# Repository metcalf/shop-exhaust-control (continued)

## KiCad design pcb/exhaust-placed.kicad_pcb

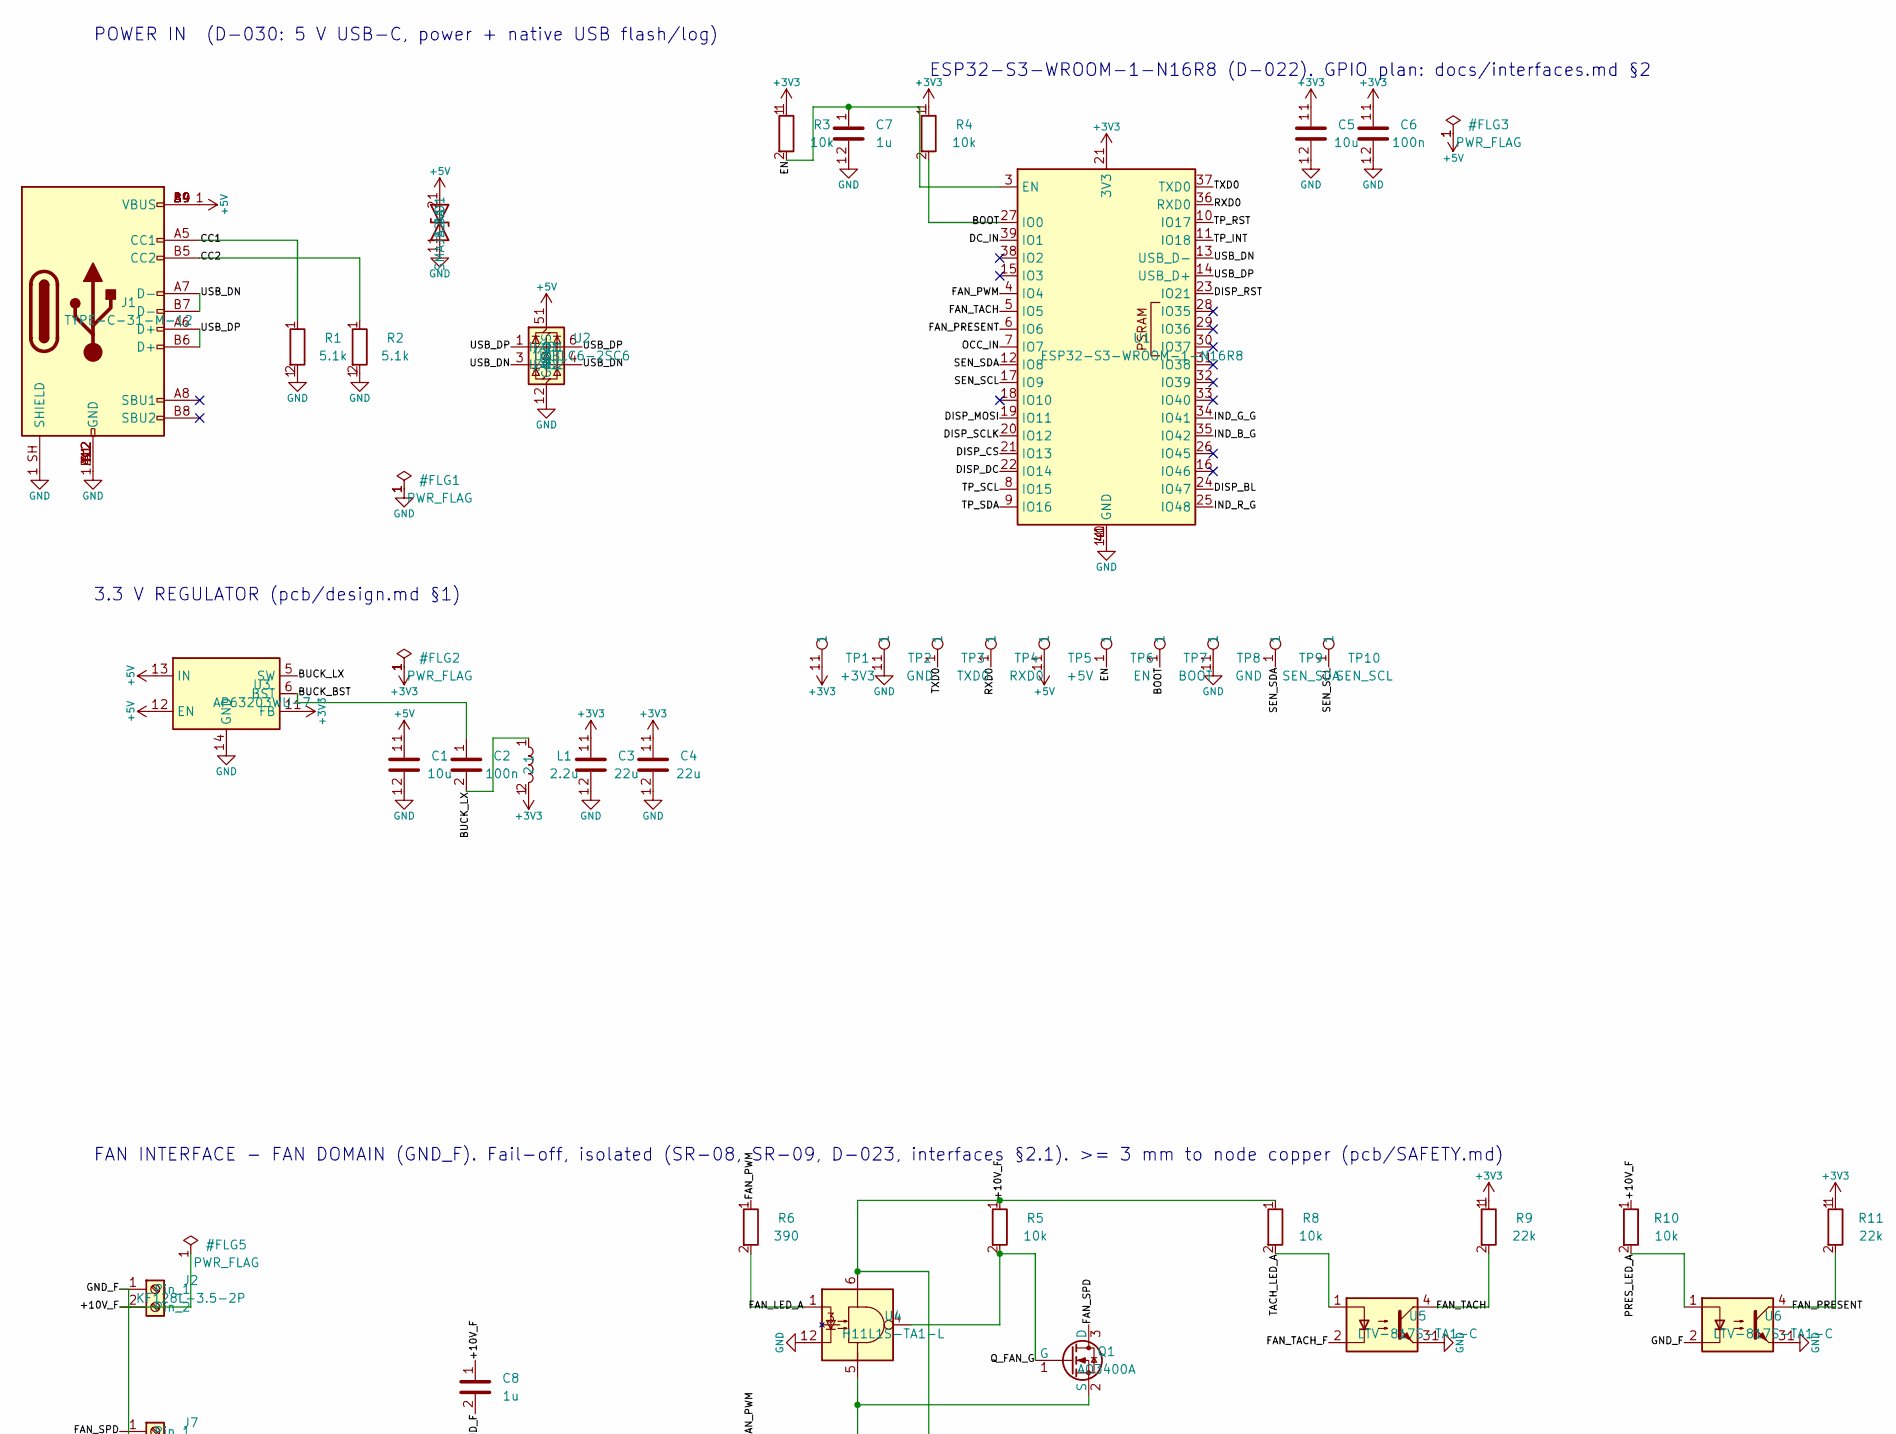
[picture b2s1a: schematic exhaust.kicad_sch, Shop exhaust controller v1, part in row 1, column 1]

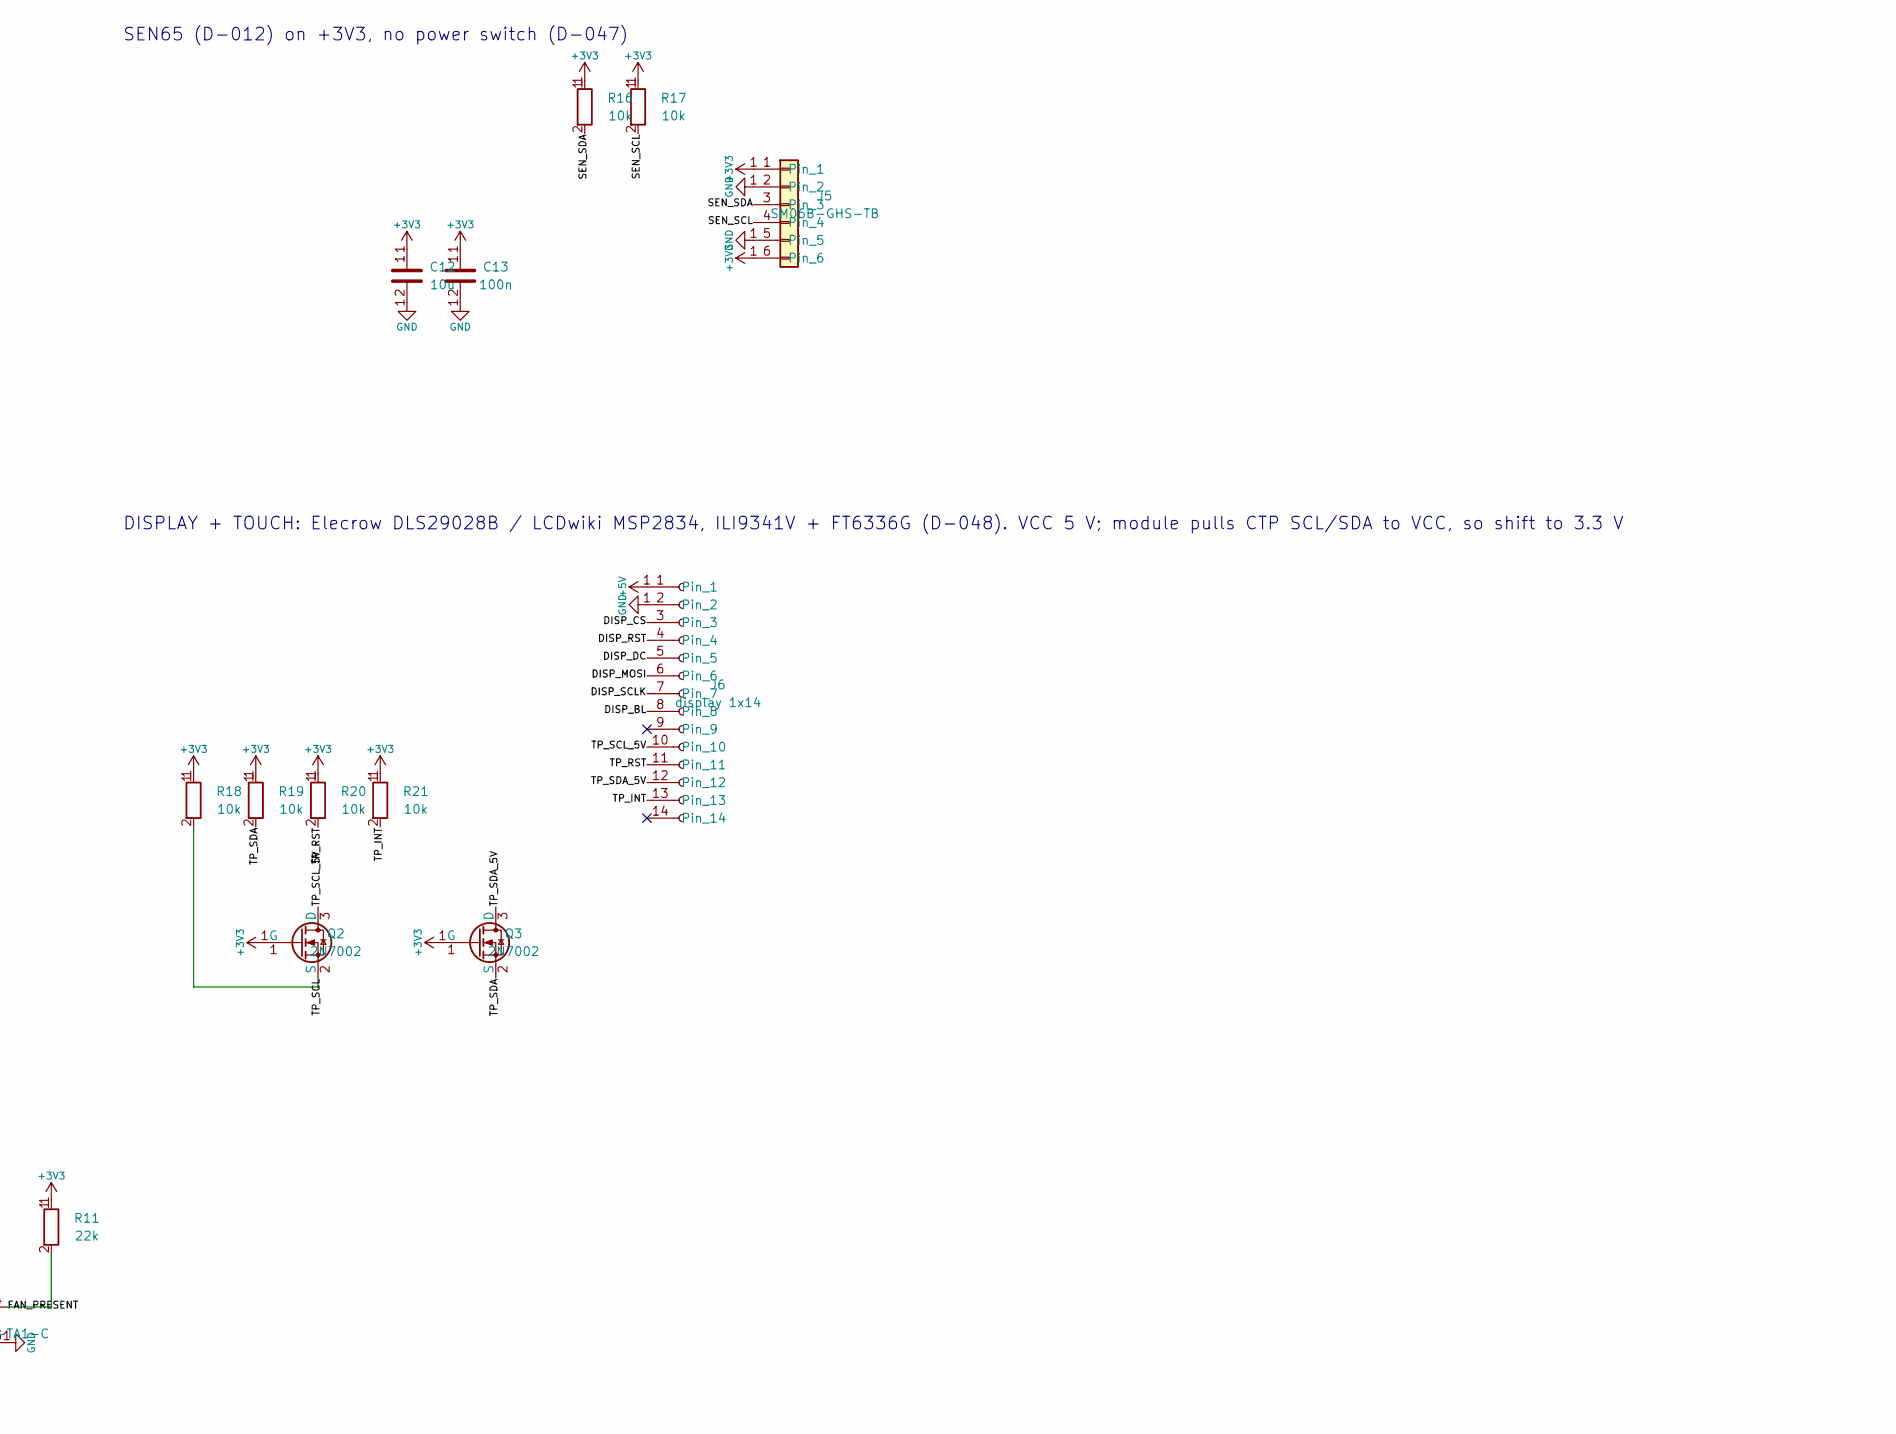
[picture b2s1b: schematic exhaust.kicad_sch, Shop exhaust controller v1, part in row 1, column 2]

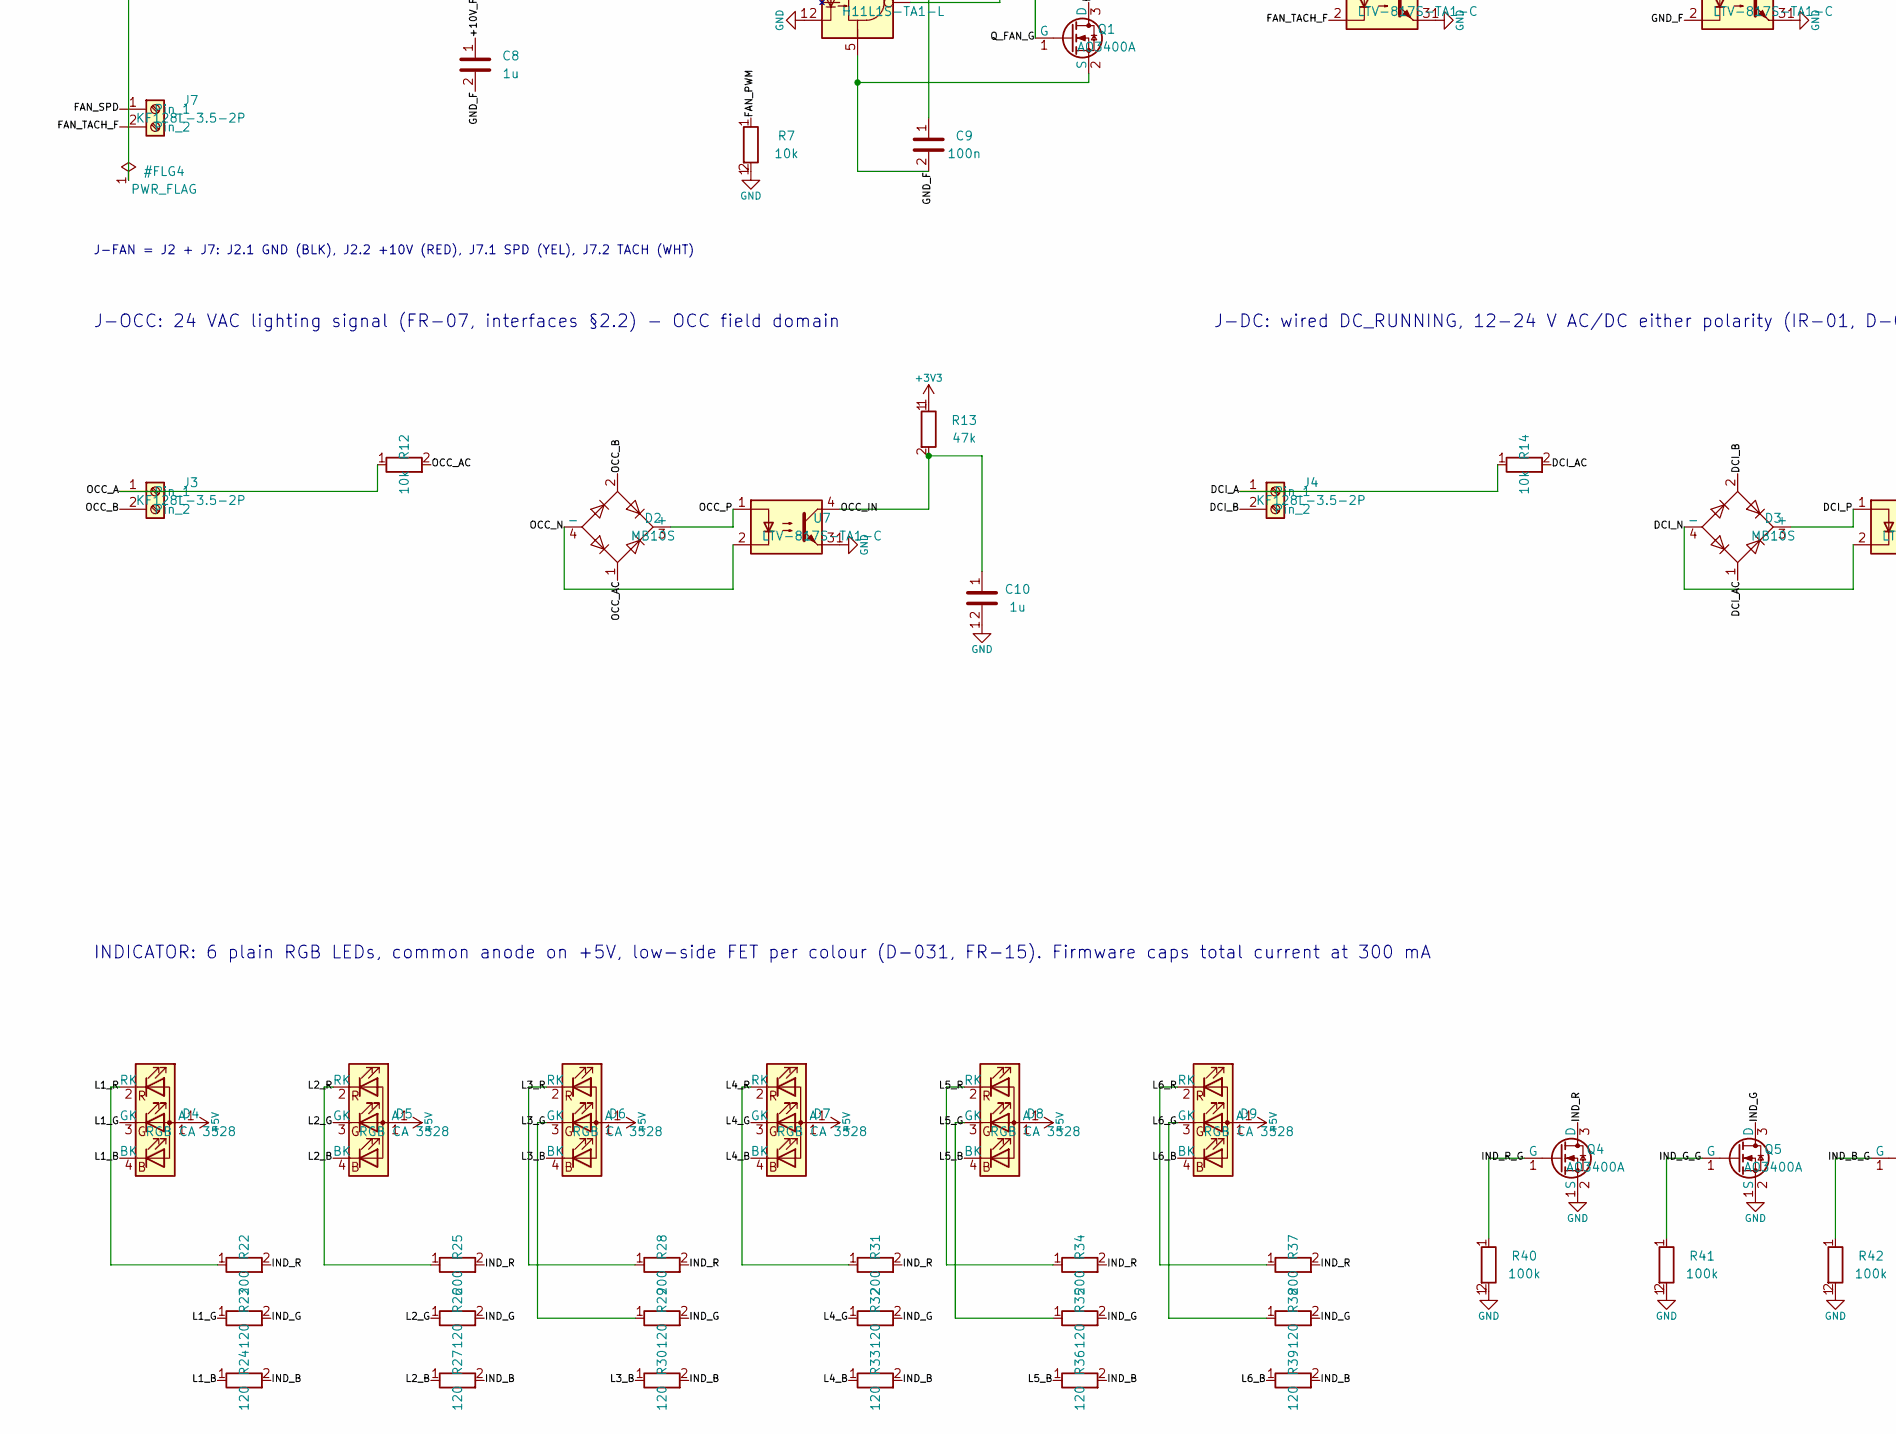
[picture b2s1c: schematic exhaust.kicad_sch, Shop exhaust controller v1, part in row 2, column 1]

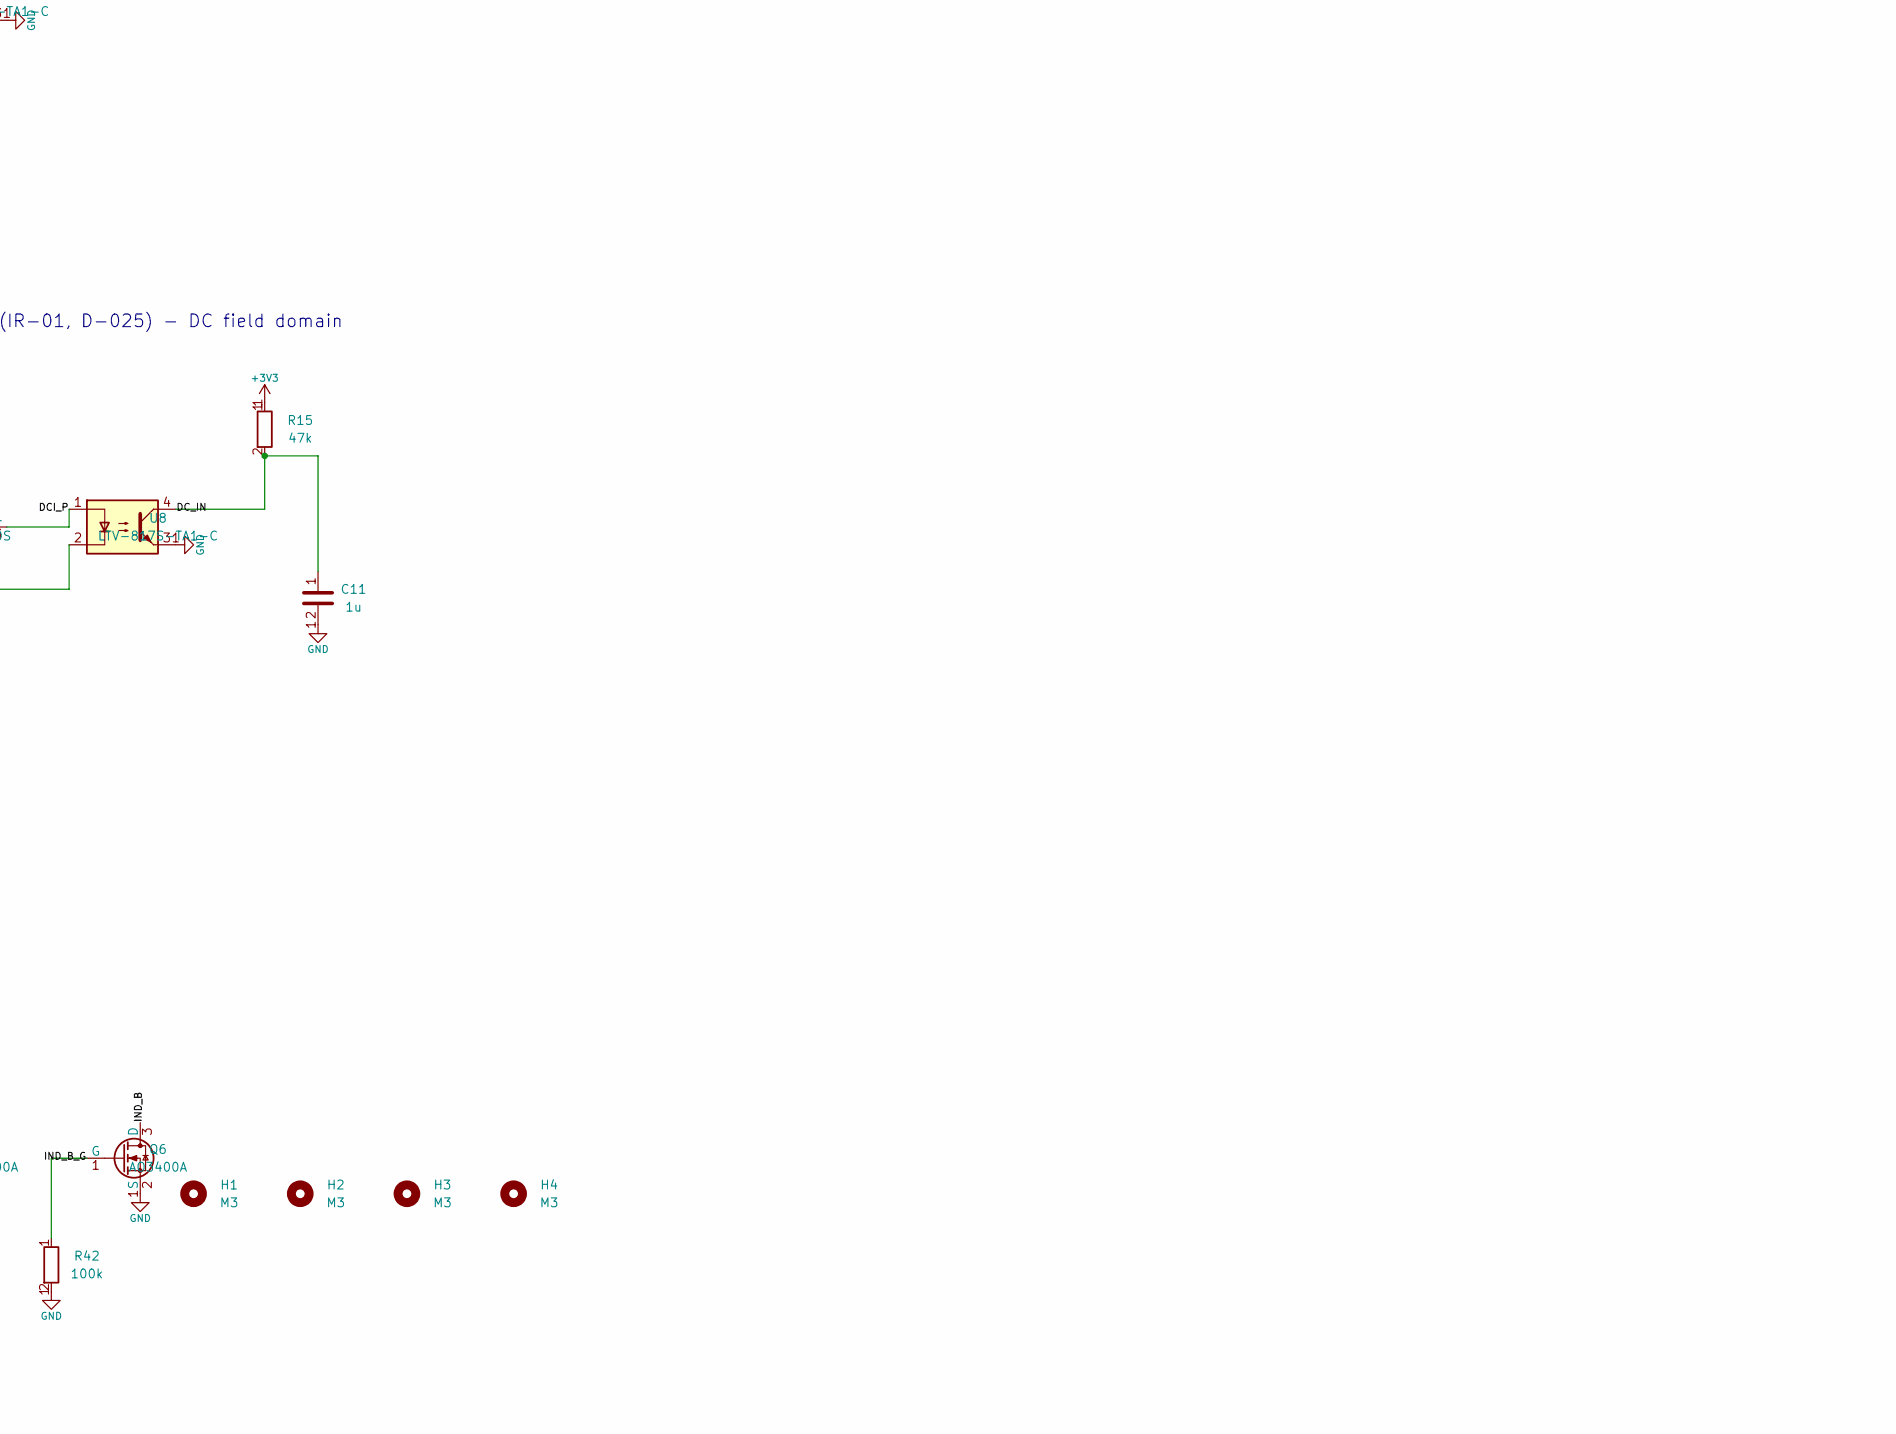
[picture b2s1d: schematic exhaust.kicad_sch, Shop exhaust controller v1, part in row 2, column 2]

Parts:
C1, C5, C12: 10u; C_0805_2012Metric
C2, C6, C9, C13: 100n; C_0603_1608Metric
C3, C4: 22u; C_1206_3216Metric
C7, C8, C10, C11: 1u; C_0603_1608Metric
D1: SMAJ5.0A; D_SMA; LCSC C113952
D2, D3: MB10S; Bridge_MBS_MB10S; LCSC C2488
D4, D5, D6, D7, D8, D9: RGB CA 3528; RGB_3528_TJ-S3528; LCSC C601699
H1, H2, H3, H4: M3; MountingHole_3.2mm_M3
J1: TYPE-C-31-M-12; USB_C_Receptacle_HRO_TYPE-C-31-M-12; LCSC C165948
J2, J3, J4, J7: KF128L-3.5-2P; TerminalBlock_KF128L-3.5-2P; LCSC C474930
J5: SM06B-GHS-TB; JST_GH_SM06B-GHS-TB_1x06-1MP_P1.25mm_Horizontal; LCSC C133065
J6: display 1x14; PinSocket_1x14_P2.54mm_Vertical; LCSC C2897377
L1: 2.2u; L_Murata_LQH44P; LCSC C135262
Q1, Q4, Q5, Q6: AO3400A; SOT-23; LCSC C20917
Q2, Q3: 2N7002; SOT-23; LCSC C8545
R1, R2: 5.1k; R_0603_1608Metric
R3, R4, R5, R7, R8, R10, R16, R17, R18, R19, R20, R21: 10k; R_0603_1608Metric
R6: 390; R_0603_1608Metric
R9, R11: 22k; R_0603_1608Metric
R12, R14: 10k; R_1206_3216Metric
R13, R15: 47k; R_0603_1608Metric
R22, R25, R28, R31, R34, R37: 200; R_0603_1608Metric
R23, R24, R26, R27, R29, R30, R32, R33, R35, R36, R38, R39: 120; R_0603_1608Metric
R40, R41, R42: 100k; R_0603_1608Metric
TP1: +3V3; TestPoint_Pad_D1.5mm
TP2, TP8: GND; TestPoint_Pad_D1.5mm
TP3: TXD0; TestPoint_Pad_D1.5mm
TP4: RXD0; TestPoint_Pad_D1.5mm
TP5: +5V; TestPoint_Pad_D1.5mm
TP6: EN; TestPoint_Pad_D1.5mm
TP7: BOOT; TestPoint_Pad_D1.5mm
TP9: SEN_SDA; TestPoint_Pad_D1.5mm
TP10: SEN_SCL; TestPoint_Pad_D1.5mm
U1: ESP32-S3-WROOM-1-N16R8; ESP32-S3-WROOM-1_NoEPADVias; LCSC C2913202
U2: USBLC6-2SC6; SOT-23-6; LCSC C2827654
U3: AP63203WU-7; TSOT-23-6; LCSC C780769
U4: H11L1S-TA1-L; SOP-6_H11L1S_LS10.2; LCSC C7435535
U5, U6, U7, U8: LTV-817S-TA1-C; SOP-4_LTV-817S_LS10.3; LCSC C109227

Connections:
+3V3: C3.1, C4.1, C5.1, C6.1, C12.1, C13.1, J5.1, J5.6, L1.2, Q2.1 (G), Q3.1 (G), R3.1, R4.1, R9.1, R11.1, R13.1, R15.1, R16.1, R17.1, R18.1, R19.1, R20.1, R21.1, TP1.1, U1.2 (3V3), U3.1 (FB)
+5V: C1.1, D1.2 (A2), D4.1 (A), D5.1 (A), D6.1 (A), D7.1 (A), D8.1 (A), D9.1 (A), J1.A4 (VBUS), J1.A9 (VBUS), J1.B4 (VBUS), J1.B9 (VBUS), J6.1, TP5.1, U2.5 (VBUS), U3.2 (EN), U3.3 (IN)
/+10V_F: C8.1, C9.1, J2.2, R5.1, R8.1, R10.1, U4.6
/BOOT: R4.2, TP7.1, U1.27 (IO0)
/BUCK_BST: C2.1, U3.6 (BST)
/BUCK_LX: C2.2, L1.1, U3.5 (SW)
/CC1: J1.A5 (CC1), R1.1
/CC2: J1.B5 (CC2), R2.1
/DCI_A: J4.1, R14.1
/DCI_AC: D3.1, R14.2
/DCI_B: D3.2, J4.2
/DCI_N: D3.4 (-), U8.2
/DCI_P: D3.3 (+), U8.1
/DC_IN: C11.1, R15.2, U1.39 (IO1), U8.4
/DISP_BL: J6.8, U1.24 (IO47)
/DISP_CS: J6.3, U1.21 (IO13)
/DISP_DC: J6.5, U1.22 (IO14)
/DISP_MOSI: J6.6, U1.19 (IO11)
/DISP_RST: J6.4, U1.23 (IO21)
/DISP_SCLK: J6.7, U1.20 (IO12)
/EN: C7.1, R3.2, TP6.1, U1.3 (EN)
/FAN_LED_A: R6.2, U4.1
/FAN_PRESENT: R11.2, U1.6 (IO6), U6.4
/FAN_PWM: R6.1, R7.1, U1.4 (IO4)
/FAN_SPD: J7.1, Q1.3 (D)
/FAN_TACH: R9.2, U1.5 (IO5), U5.4
/FAN_TACH_F: J7.2, U5.2
/GND_F: C8.2, C9.2, J2.1, Q1.2 (S), U4.5, U6.2
/IND_B: Q6.3 (D), R24.2, R27.2, R30.2, R33.2, R36.2, R39.2
/IND_B_G: Q6.1 (G), R42.1, U1.35 (IO42)
/IND_G: Q5.3 (D), R23.2, R26.2, R29.2, R32.2, R35.2, R38.2
/IND_G_G: Q5.1 (G), R41.1, U1.34 (IO41)
/IND_R: Q4.3 (D), R22.2, R25.2, R28.2, R31.2, R34.2, R37.2
/IND_R_G: Q4.1 (G), R40.1, U1.25 (IO48)
/L1_B: D4.4 (BK), R24.1
/L1_G: D4.3 (GK), R23.1
/L1_R: D4.2 (RK), R22.1
/L2_B: D5.4 (BK), R27.1
/L2_G: D5.3 (GK), R26.1
/L2_R: D5.2 (RK), R25.1
/L3_B: D6.4 (BK), R30.1
/L3_G: D6.3 (GK), R29.1
/L3_R: D6.2 (RK), R28.1
/L4_B: D7.4 (BK), R33.1
/L4_G: D7.3 (GK), R32.1
/L4_R: D7.2 (RK), R31.1
/L5_B: D8.4 (BK), R36.1
/L5_G: D8.3 (GK), R35.1
/L5_R: D8.2 (RK), R34.1
/L6_B: D9.4 (BK), R39.1
/L6_G: D9.3 (GK), R38.1
/L6_R: D9.2 (RK), R37.1
/OCC_A: J3.1, R12.1
/OCC_AC: D2.1, R12.2
/OCC_B: D2.2, J3.2
/OCC_IN: C10.1, R13.2, U1.7 (IO7), U7.4
/OCC_N: D2.4 (-), U7.2
/OCC_P: D2.3 (+), U7.1
/PRES_LED_A: R10.2, U6.1
/Q_FAN_G: Q1.1 (G), R5.2, U4.4
/RXD0: TP4.1, U1.36 (RXD0)
/SEN_SCL: J5.4, R17.2, TP10.1, U1.17 (IO9)
/SEN_SDA: J5.3, R16.2, TP9.1, U1.12 (IO8)
/TACH_LED_A: R8.2, U5.1
/TP_INT: J6.13, R21.2, U1.11 (IO18)
/TP_RST: J6.11, R20.2, U1.10 (IO17)
/TP_SCL: Q2.2 (S), R18.2, U1.8 (IO15)
/TP_SCL_5V: J6.10, Q2.3 (D)
/TP_SDA: Q3.2 (S), R19.2, U1.9 (IO16)
/TP_SDA_5V: J6.12, Q3.3 (D)
/TXD0: TP3.1, U1.37 (TXD0)
/USB_DN: J1.A7 (D-), J1.B7 (D-), U1.13 (USB_D-), U2.3 (I/O2), U2.4 (I/O2)
/USB_DP: J1.A6 (D+), J1.B6 (D+), U1.14 (USB_D+), U2.1 (I/O1), U2.6 (I/O1)
GND: C1.2, C3.2, C4.2, C5.2, C6.2, C7.2, C10.2, C11.2, C12.2, C13.2, D1.1 (A1), J1.A1 (GND), J1.A12 (GND), J1.B1 (GND), J1.B12 (GND), J1.SH (SHIELD), J5.2, J5.5, J6.2, Q4.2 (S), Q5.2 (S), Q6.2 (S), R1.2, R2.2, R7.2, R40.2, R41.2, R42.2, TP2.1, TP8.1, U1.1 (GND), U1.40 (GND), U1.41 (GND), U2.2 (GND), U3.4 (GND), U4.2, U5.3, U6.3, U7.3, U8.3

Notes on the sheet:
POWER IN (D-030: 5 V USB-C, power + native USB flash/log)
3.3 V REGULATOR (pcb/design.md §1)
ESP32-S3-WROOM-1-N16R8 (D-022). GPIO plan: docs/interfaces.md §2
FAN INTERFACE - FAN DOMAIN (GND_F). Fail-off, isolated (SR-08, SR-09, D-023, interfaces §2.1). >= 3 mm to node copper (pcb/SAFETY.md)
J-FAN = J2 + J7: J2.1 GND (BLK), J2.2 +10V (RED), J7.1 SPD (YEL), J7.2 TACH (WHT)
J-OCC: 24 VAC lighting signal (FR-07, interfaces §2.2) - OCC field domain
J-DC: wired DC_RUNNING, 12-24 V AC/DC either polarity (IR-01, D-025) - DC field domain
SEN65 (D-012) on +3V3, no power switch (D-047)
DISPLAY + TOUCH: Elecrow DLS29028B / LCDwiki MSP2834, ILI9341V + FT6336G (D-048). VCC 5 V; module pulls CTP SCL/SDA to VCC, so shift to 3.3 V
INDICATOR: 6 plain RGB LEDs, common anode on +5V, low-side FET per colour (D-031, FR-15). Firmware caps total current at 300 mA

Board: 2 copper layers, 100 parts (10 on the bottom side), 74 nets, no tracks yet.

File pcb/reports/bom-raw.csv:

"Reference","Value","Footprint","LCSC","QUANTITY"
"C1,C5,C12","10u","Capacitor_SMD:C_0805_2012Metric","","3"
"C2,C6,C9,C13","100n","Capacitor_SMD:C_0603_1608Metric","","4"
"C3,C4","22u","Capacitor_SMD:C_1206_3216Metric","","2"
"C7,C8,C10,C11","1u","Capacitor_SMD:C_0603_1608Metric","","4"
"D1","SMAJ5.0A","Diode_SMD:D_SMA","C113952","1"
"D2,D3","MB10S","exhaust:Bridge_MBS_MB10S","C2488","2"
"D4-D9","RGB CA 3528","exhaust:RGB_3528_TJ-S3528","C601699","6"
"H1-H4","M3","MountingHole:MountingHole_3.2mm_M3","","4"
"J1","TYPE-C-31-M-12","Connector_USB:USB_C_Receptacle_HRO_TYPE-C-31-M-12","C165948","1"
"J2-J4,J7","KF128L-3.5-2P","exhaust:TerminalBlock_KF128L-3.5-2P","C474930","4"
"J5","SM06B-GHS-TB","Connector_JST:JST_GH_SM06B-GHS-TB_1x06-1MP_P1.25mm_Horizontal","C133065","1"
"J6","display 1x14","Connector_PinSocket_2.54mm:PinSocket_1x14_P2.54mm_Vertical","C2897377","1"
"L1","2.2u","exhaust:L_Murata_LQH44P","C135262","1"
"Q1,Q4-Q6","AO3400A","Package_TO_SOT_SMD:SOT-23","C20917","4"
"Q2,Q3","2N7002","Package_TO_SOT_SMD:SOT-23","C8545","2"
"R1,R2","5.1k","Resistor_SMD:R_0603_1608Metric","","2"
"R3-R5,R7,R8,R10,R16-R21","10k","Resistor_SMD:R_0603_1608Metric","","12"
"R6","390","Resistor_SMD:R_0603_1608Metric","","1"
"R9,R11","22k","Resistor_SMD:R_0603_1608Metric","","2"
"R12,R14","10k","Resistor_SMD:R_1206_3216Metric","","2"
"R13,R15","47k","Resistor_SMD:R_0603_1608Metric","","2"
"R22,R25,R28,R31,R34,R37","200","Resistor_SMD:R_0603_1608Metric","","6"
"R23,R24,R26,R27,R29,R30,R32,R33,R35,R36,R38,R39","120","Resistor_SMD:R_0603_1608Metric","","12"
"R40-R42","100k","Resistor_SMD:R_0603_1608Metric","","3"
"TP1","+3V3","TestPoint:TestPoint_Pad_D1.5mm","","1"
"TP2,TP8","GND","TestPoint:TestPoint_Pad_D1.5mm","","2"
"TP3","TXD0","TestPoint:TestPoint_Pad_D1.5mm","","1"
"TP4","RXD0","TestPoint:TestPoint_Pad_D1.5mm","","1"
"TP5","+5V","TestPoint:TestPoint_Pad_D1.5mm","","1"
"TP6","EN","TestPoint:TestPoint_Pad_D1.5mm","","1"
"TP7","BOOT","TestPoint:TestPoint_Pad_D1.5mm","","1"
"TP9","SEN_SDA","TestPoint:TestPoint_Pad_D1.5mm","","1"
"TP10","SEN_SCL","TestPoint:TestPoint_Pad_D1.5mm","","1"
"U1","ESP32-S3-WROOM-1-N16R8","exhaust:ESP32-S3-WROOM-1_NoEPADVias","C2913202","1"
"U2","USBLC6-2SC6","Package_TO_SOT_SMD:SOT-23-6","C2827654","1"
"U3","AP63203WU-7","Package_TO_SOT_SMD:TSOT-23-6","C780769","1"
"U4","H11L1S-TA1-L","exhaust:SOP-6_H11L1S_LS10.2","C7435535","1"
"U5-U8","LTV-817S-TA1-C","exhaust:SOP-4_LTV-817S_LS10.3","C109227","4"

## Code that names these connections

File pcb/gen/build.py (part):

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res("10k", (X + 85, Y + 30), "FAN_PWM", "GND")
# Tach: white low -> LED lit -> FAN_TACH low
res("10k", (X + 160, Y - 5), "+10V_F", "TACH_LED_A")
part("PC817", (X + 175, Y + 10), {"1": "TACH_LED_A", "2": "FAN_TACH_F", "3": "GND", "4": "FAN_TACH"})
res("22k", (X + 190, Y - 5), "+3V3", "FAN_TACH")
# Presence: fan side powered -> LED lit -> FAN_PRESENT low
res("10k", (X + 210, Y - 5), "+10V_F", "PRES_LED_A")
part("PC817", (X + 225, Y + 10), {"1": "PRES_LED_A", "2": "GND_F", "3": "GND", "4": "FAN_PRESENT"})
res("22k", (X + 240, Y - 5), "+3V3", "FAN_PRESENT")

# ---------------------------------------------------------------- 24 VAC / DC inputs (field domains)
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X, Y = 300, 110
sh.note("DISPLAY + TOUCH: Elecrow DLS29028B / LCDwiki MSP2834, ILI9341V + FT6336G (D-048). "
        "VCC 5 V; module pulls CTP SCL/SDA to VCC, so shift to 3.3 V", (X - 10, Y - 15))
part("DISP_HDR", (X + 70, Y + 10), {"Pin_1": "+5V", "Pin_2": "GND", "Pin_3": "DISP_CS",
                                    "Pin_4": "DISP_RST", "Pin_5": "DISP_DC", "Pin_6": "DISP_MOSI",
                                    "Pin_7": "DISP_SCLK", "Pin_8": "DISP_BL", "Pin_10": "TP_SCL_5V",
                                    "Pin_11": "TP_RST", "Pin_12": "TP_SDA_5V", "Pin_13": "TP_INT"},
     nc=("Pin_9", "Pin_14"), r="J6")
# Bidirectional open-drain shifters. 2N7002 for its low Ciss, not the AO3400A (D-048).
for i, n in enumerate(["TP_SCL", "TP_SDA"]):
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
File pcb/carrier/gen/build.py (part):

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sh.begin("hdr")
X, Y = 40, 50
sh.note("J1: WAVESHARE ESP32-S3-Touch-LCD-3.5 J8 (2x16, 2.54 mm), Rev 2.0 numbering. 6 GPIO21, 8 GPIO38, "
        "10 GPIO39, 12 GPIO40, 14 GPIO41, 16 GPIO42, 23 PWRON, 25/27 I2C SCL/SDA (GPIO7/8)", (X - 20, Y - 25))
sh.note("Hand-soldered pin header into the board's female J8. V1 boards number the rows oppositely (same "
        "positions): check orientation against the STEP at layout.", (X - 20, Y - 20), size=1.27)
part("HDR", (X, Y), {str(k): v for k, v in J1.items()}, nc=[str(k) for k in J1_NC], r="J1", dnp=True)
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# PWM: Q1 holds yellow low (fan off) unless U1's LED is lit
res("390", (X + 75, Y - 5), "FAN_PWM", "FAN_LED_A")
res("10k", (X + 75, Y + 30), "FAN_PWM", "GND")
part("PC817", (X + 100, Y + 10), {"1": "FAN_LED_A", "2": "GND", "3": "GND_F", "4": "Q_FAN_G"}, r="U1")
res("2.2k", (X + 120, Y - 5), "+10V_F", "Q_FAN_G")
part("NFET_LL", (X + 135, Y + 15), {"G": "Q_FAN_G", "D": "FAN_SPD", "S": "GND_F"}, r="Q1")
# Tach: white low -> LED lit -> FAN_TACH low
res("10k", (X + 165, Y - 5), "+10V_F", "TACH_LED_A")
part("PC817", (X + 180, Y + 10), {"1": "TACH_LED_A", "2": "FAN_TACH_F", "3": "GND", "4": "FAN_TACH"}, r="U2")
res("22k", (X + 195, Y - 5), "+3V3", "FAN_TACH")
# Presence: fan side powered -> LED lit -> FAN_PRESENT low
res("10k", (X + 215, Y - 5), "+10V_F", "PRES_LED_A")
part("PC817", (X + 230, Y + 10), {"1": "PRES_LED_A", "2": "GND_F", "3": "GND", "4": "FAN_PRESENT"}, r="U3")
res("22k", (X + 245, Y - 5), "+3V3", "FAN_PRESENT")

# ---------------------------------------------------------------- 24 VAC / DC inputs (field domains)
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
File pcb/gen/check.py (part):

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              f"{r}: transistor not node-side")

# --- fail-off (SR-08): Q_FAN gate pulled up to +10V_F, drain on the speed line --------
qfan = sorted({r for r, _p in pin_net if net_of(r, 3) == "FAN_SPD" and r.startswith("Q")})
check(len(qfan) == 1, "one FET on FAN_SPD")
if qfan:
    q = qfan[0]
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check(has_res("EN", "+3V3"), "EN pull-up")

# --- GPIO plan (docs/interfaces.md §2) ------------------------------------------
GPIO = {"IO1": "DC_IN", "IO4": "FAN_PWM", "IO5": "FAN_TACH", "IO6": "FAN_PRESENT",
        "IO7": "OCC_IN", "IO8": "SEN_SDA", "IO9": "SEN_SCL",
        "IO11": "DISP_MOSI", "IO12": "DISP_SCLK", "IO13": "DISP_CS", "IO14": "DISP_DC", "IO21": "DISP_RST",
        "IO47": "DISP_BL", "IO15": "TP_SCL", "IO16": "TP_SDA", "IO17": "TP_RST", "IO18": "TP_INT",
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check(len(buck) == 1, "one AP63203")
if buck:
    # TSOT-26: 1 FB, 2 EN, 3 VIN, 4 GND, 5 SW, 6 BST
    for pin, want in ((1, "+3V3"), (2, "+5V"), (3, "+5V"), (4, "GND"), (5, "BUCK_LX"), (6, "BUCK_BST")):
        check(net_of(buck[0], pin) == want, f"{buck[0]} pin {pin} should be {want}, is {net_of(buck[0], pin)}")
check(any({net_of(c, 1), net_of(c, 2)} == {"BUCK_BST", "BUCK_LX"} for c in refs_on("BUCK_BST") if c.startswith("C")),
      "BST cap to SW")
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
